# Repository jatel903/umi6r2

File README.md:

# UMI6R2
## Universal modbus inputs module
###### jatel.sk
**Specification:**  
Supply: 12 - 30V / 50mA  
Core: Arduino Nano  
Number of inputs: 6  
Input types: TTL / TTL with pull-up 2k2 / 0-10V / 1-10V / 0-20mA / 4-20mA  
Number of outputs: 2  
Output types: relay contact 10A/240VAC  
Communication: Modbus RTU 485  
Mounting: [DIN 4M](https://www.tme.eu/sk/en/details/4mh53_5/din-rail-mounting-enclosures/italtronic/)  

#### Description
Low cost universal modbus controll unit for low cost sensors and actuators from China:  
[NTC](https://www.aliexpress.com/item/1005001645557005.html?spm=a2g0o.productlist.0.0.187f54f5sMFDxZ&algo_pvid=9de88852-8f4a-408b-ad87-1dfdc50c90a6&algo_expid=9de88852-8f4a-408b-ad87-1dfdc50c90a6-12&btsid=2100bb5116140376819446860eae3f&ws_ab_test=searchweb0_0,searchweb201602_,searchweb201603_)  
 [Hall Flow Sensor](https://www.aliexpress.com/item/1005001652070023.html?spm=a2g0o.productlist.0.0.111d3f4bfW8KI7&algo_pvid=0e9d849e-a274-4857-9695-266535420252&algo_expid=0e9d849e-a274-4857-9695-266535420252-3&btsid=0b0a0ae216140368139255250ee091&ws_ab_test=searchweb0_0,searchweb201602_,searchweb201603_)  
[DHT22](https://www.aliexpress.com/item/32759901711.html?spm=a2g0o.productlist.0.0.7c9b27acyKxgzN&algo_pvid=cdfb1f8e-0449-4fde-b37e-72250bef6eec&algo_expid=cdfb1f8e-0449-4fde-b37e-72250bef6eec-1&btsid=2100bddf16140369182308517e6039&ws_ab_test=searchweb0_0,searchweb201602_,searchweb201603_)  
[DS18B20](https://www.aliexpress.com/item/4000895660165.html?spm=a2g0o.productlist.0.0.6e117a31a0Jav1&algo_pvid=1cb9bcee-23eb-4e23-812d-128fc839b4cb&algo_expid=1cb9bcee-23eb-4e23-812d-128fc839b4cb-4&btsid=2100bb5116140369607362637eb05f&ws_ab_test=searchweb0_0,searchweb201602_,searchweb201603_)  
[Pressure Sensor](https://www.aliexpress.com/item/1447040260.html?spm=a2g0o.productlist.0.0.542b418eIxJRxZ&algo_pvid=66da158e-1870-4b2f-a303-d273c240283c&algo_expid=66da158e-1870-4b2f-a303-d273c240283c-0&btsid=2100bdd516140372507935255e4c69&ws_ab_test=searchweb0_0,searchweb201602_,searchweb201603_)  
[Electric Valve](https://www.aliexpress.com/item/4000279793000.html?spm=a2g0o.productlist.0.0.721212089kHY2M&algo_pvid=9ae05a60-6b6b-4111-a46f-0fc823cf62b9&algo_expid=9ae05a60-6b6b-4111-a46f-0fc823cf62b9-30&btsid=0bb0624316140370036014582e4170&ws_ab_test=searchweb0_0,searchweb201602_,searchweb201603_)  
[Electric Solenoid Valve](https://www.aliexpress.com/item/4000067341651.html?spm=a2g0o.productlist.0.0.721212089kHY2M&algo_pvid=9ae05a60-6b6b-4111-a46f-0fc823cf62b9&algo_expid=9ae05a60-6b6b-4111-a46f-0fc823cf62b9-31&btsid=0bb0624316140370036014582e4170&ws_ab_test=searchweb0_0,searchweb201602_,searchweb201603_)  
etc...

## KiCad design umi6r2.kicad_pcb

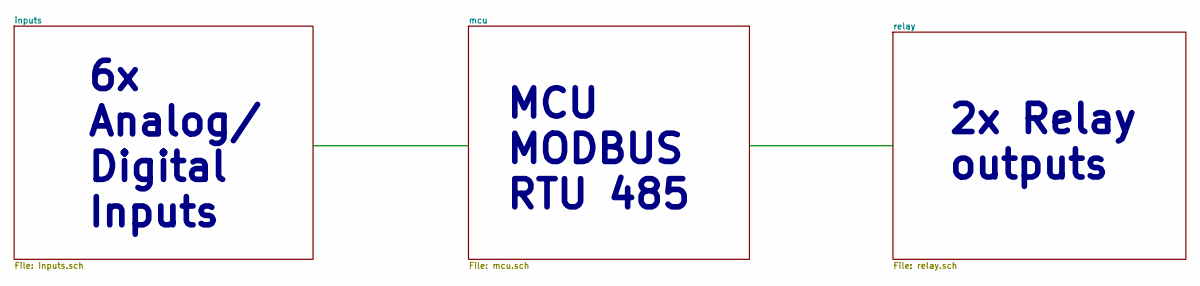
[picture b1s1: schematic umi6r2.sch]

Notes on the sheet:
MCU MODBUS RTU 485
2x Relay outputs
6x Analog/ Digital Inputs

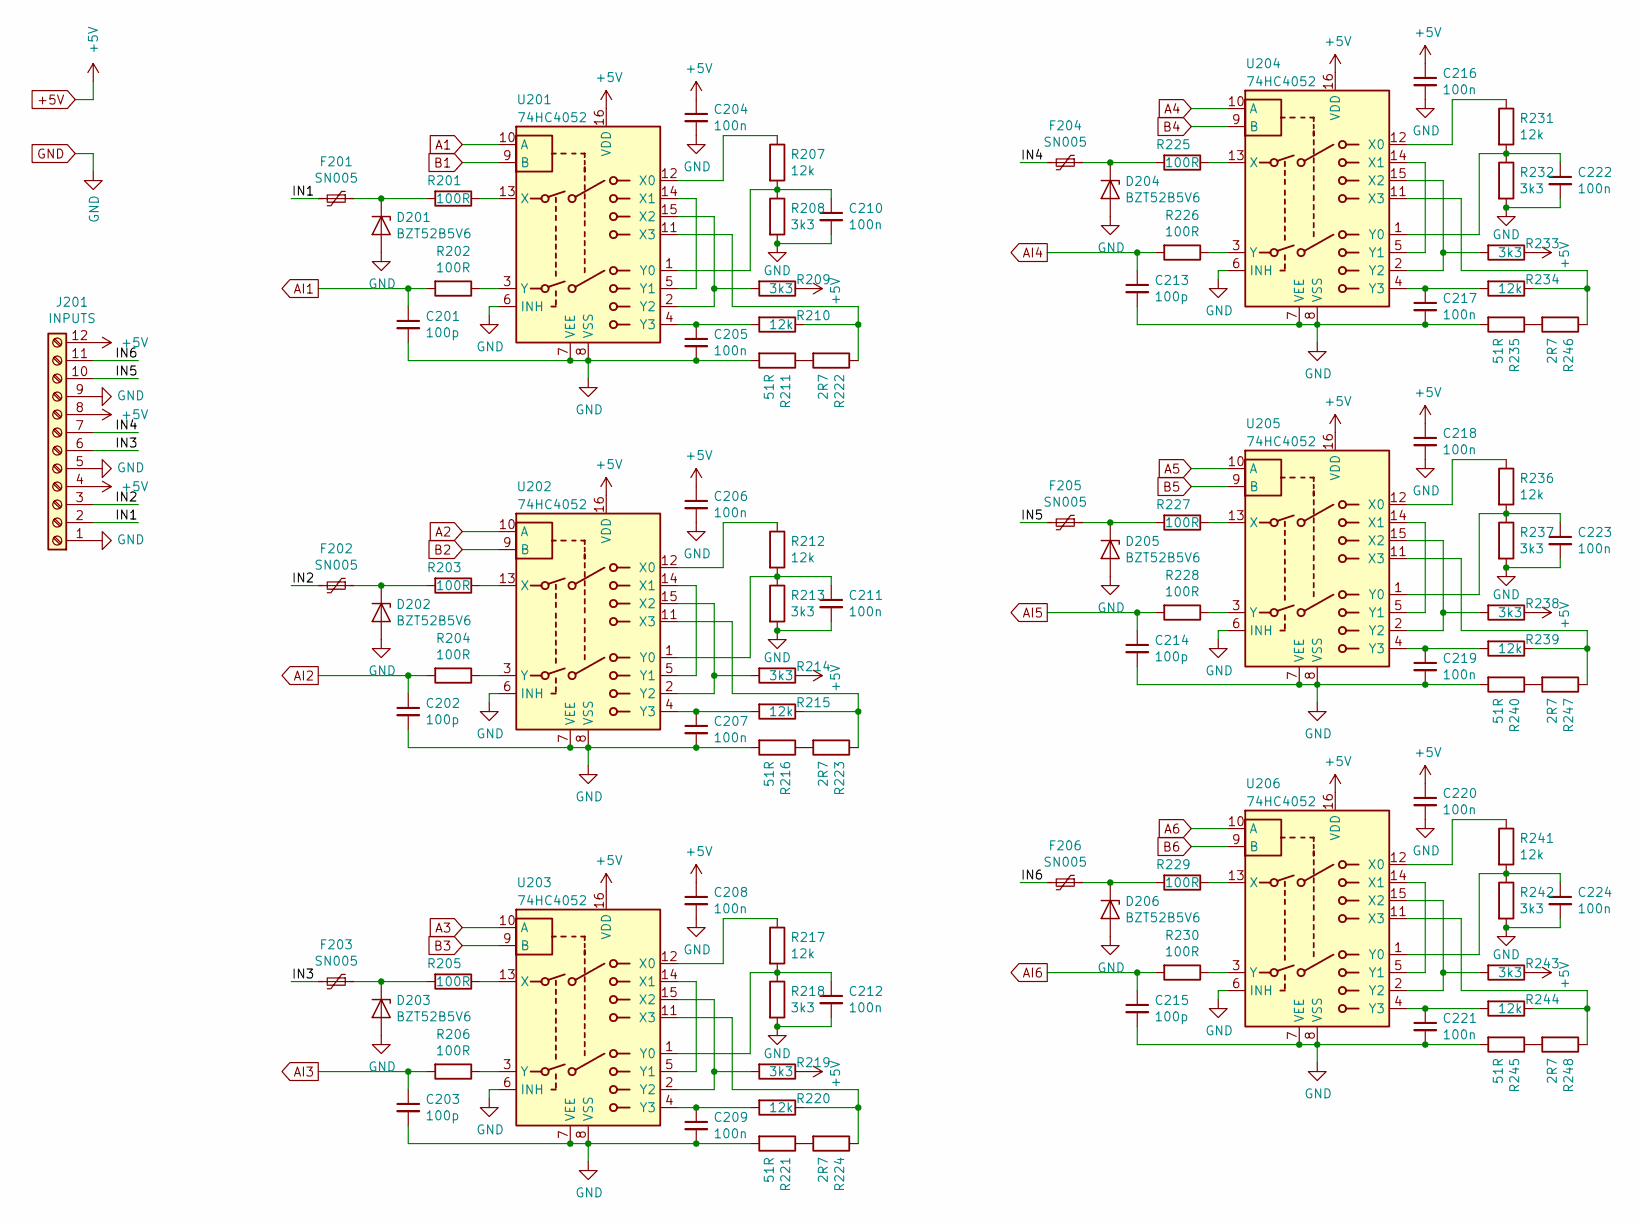
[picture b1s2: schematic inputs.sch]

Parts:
C201, C202, C203, C213, C214, C215: 100p; C_0805_2012Metric_Pad1.15x1.40mm_HandSolder
C204, C205, C206, C207, C208, C209, C210, C211, C212, C216, C217, C218, C219, C220, C221, C222, C223, C224: 100n; C_0805_2012Metric_Pad1.15x1.40mm_HandSolder
D201, D202, D203, D204, D205, D206: BZT52B5V6; D_SOD-123
F201, F202, F203, F204, F205, F206: SN005; R_1206_3216Metric_Pad1.42x1.75mm_HandSolder
J201: INPUTS; TerminalBlock_Phoenix_MKDS-1,5-12-5.08_1x12_P5.08mm_Horizon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
R201, R202, R203, R204, R205, R206, R225, R226, R227, R228, R229, R230: 100R; R_0805_2012Metric_Pad1.15x1.40mm_HandSolder
R207, R210, R212, R215, R217, R220, R231, R234, R236, R239, R241, R244: 12k; R_0805_2012Metric_Pad1.15x1.40mm_HandSolder
R208, R209, R213, R214, R218, R219, R232, R233, R237, R238, R242, R243: 3k3; R_0805_2012Metric_Pad1.15x1.40mm_HandSolder
R211, R216, R221, R235, R240, R245: 51R; R_0805_2012Metric_Pad1.15x1.40mm_HandSolder
R222, R223, R224, R246, R247, R248: 2R7; R_0805_2012Metric_Pad1.15x1.40mm_HandSolder
U201, U202, U203, U204, U205, U206: 74HC4052; SOIC-16_3.9x9.9mm_P1.27mm

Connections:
+5V: C204.1, C206.1, C208.1, C216.1, C218.1, C220.1, J201.4, J201.8, J201.12, R209.1, R214.1, R219.1, R233.1, R238.1, R243.1, U201.16 (VDD), U202.16 (VDD), U203.16 (VDD), U204.16 (VDD), U205.16 (VDD), U206.16 (VDD); also elsewhere on the board
/inputs/IN1: F201.2, J201.2
/inputs/IN2: F202.2, J201.3
/inputs/IN3: F203.2, J201.6
/inputs/IN4: F204.2, J201.7
/inputs/IN5: F205.2, J201.10
/inputs/IN6: F206.2, J201.11
A1: U201.10 (A); also elsewhere on the board
A2: U202.10 (A); also elsewhere on the board
A3: U203.10 (A); also elsewhere on the board
A4: U204.10 (A); also elsewhere on the board
A5: U205.10 (A); also elsewhere on the board
A6: U206.10 (A); also elsewhere on the board
AI1: C201.1, R202.2; also elsewhere on the board
AI2: C202.1, R204.2; also elsewhere on the board
AI3: C203.1, R206.2; also elsewhere on the board
AI4: C213.1, R226.2; also elsewhere on the board
AI5: C214.1, R228.2; also elsewhere on the board
AI6: C215.1, R230.2; also elsewhere on the board
B1: U201.9 (B); also elsewhere on the board
B2: U202.9 (B); also elsewhere on the board
B3: U203.9 (B); also elsewhere on the board
B4: U204.9 (B); also elsewhere on the board
B5: U205.9 (B); also elsewhere on the board
B6: U206.9 (B); also elsewhere on the board
GND: C201.2, C202.2, C203.2, C204.2, C205.2, C206.2, C207.2, C208.2, C209.2, C210.2, C211.2, C212.2, C213.2, C214.2, C215.2, C216.2, C217.2, C218.2, C219.2, C220.2, C221.2, C222.2, C223.2, C224.2, D201.2 (A), D202.2 (A), D203.2 (A), D204.2 (A), D205.2 (A), D206.2 (A), J201.1, J201.5, J201.9, R208.2, R211.2, R213.2, R216.2, R218.2, R221.2, R232.2, R235.2, R237.2, R240.2, R242.2, R245.2, U201.6 (INH), U201.7 (VEE), U201.8 (VSS), U202.6 (INH), U202.7 (VEE), U202.8 (VSS), U203.6 (INH), U203.7 (VEE), U203.8 (VSS), U204.6 (INH), U204.7 (VEE), U204.8 (VSS), U205.6 (INH), U205.7 (VEE), U205.8 (VSS), U206.6 (INH), U206.7 (VEE), U206.8 (VSS); also elsewhere on the board
unnamed: C205.1, R210.2, U201.4 (Y3)
unnamed: C207.1, R215.2, U202.4 (Y3)
unnamed: C209.1, R220.2, U203.4 (Y3)
unnamed: C210.1, R207.2, R208.1, U201.1 (Y0)
unnamed: C211.1, R212.2, R213.1, U202.1 (Y0)
unnamed: C212.1, R217.2, R218.1, U203.1 (Y0)
unnamed: C217.1, R234.2, U204.4 (Y3)
unnamed: C219.1, R239.2, U205.4 (Y3)
unnamed: C221.1, R244.2, U206.4 (Y3)
unnamed: C222.1, R231.2, R232.1, U204.1 (Y0)
unnamed: C223.1, R236.2, R237.1, U205.1 (Y0)
unnamed: C224.1, R241.2, R242.1, U206.1 (Y0)
unnamed: D201.1 (K), F201.1, R201.2
unnamed: D202.1 (K), F202.1, R203.2
unnamed: D203.1 (K), F203.1, R205.2
unnamed: D204.1 (K), F204.1, R225.2
unnamed: D205.1 (K), F205.1, R227.2
unnamed: D206.1 (K), F206.1, R229.2
unnamed: R201.1, U201.13 (X)
unnamed: R202.1, U201.3 (Y)
unnamed: R203.1, U202.13 (X)
unnamed: R204.1, U202.3 (Y)
unnamed: R205.1, U203.13 (X)
unnamed: R206.1, U203.3 (Y)
unnamed: R207.1, U201.12 (X0)
unnamed: R209.2, U201.2 (Y2), U201.15 (X2)
unnamed: R210.1, R222.1, U201.11 (X3)
unnamed: R211.1, R222.2
unnamed: R212.1, U202.12 (X0)
unnamed: R214.2, U202.2 (Y2), U202.15 (X2)
unnamed: R215.1, R223.1, U202.11 (X3)
unnamed: R216.1, R223.2
unnamed: R217.1, U203.12 (X0)
unnamed: R219.2, U203.2 (Y2), U203.15 (X2)
unnamed: R220.1, R224.1, U203.11 (X3)
unnamed: R221.1, R224.2
unnamed: R225.1, U204.13 (X)
unnamed: R226.1, U204.3 (Y)
unnamed: R227.1, U205.13 (X)
unnamed: R228.1, U205.3 (Y)
unnamed: R229.1, U206.13 (X)
unnamed: R230.1, U206.3 (Y)
unnamed: R231.1, U204.12 (X0)
unnamed: R233.2, U204.2 (Y2), U204.15 (X2)
unnamed: R234.1, R246.1, U204.11 (X3)
unnamed: R235.1, R246.2
unnamed: R236.1, U205.12 (X0)
unnamed: R238.2, U205.2 (Y2), U205.15 (X2)
unnamed: R239.1, R247.1, U205.11 (X3)
unnamed: R240.1, R247.2
unnamed: R241.1, U206.12 (X0)
unnamed: R243.2, U206.2 (Y2), U206.15 (X2)
unnamed: R244.1, R248.1, U206.11 (X3)
unnamed: R245.1, R248.2
unnamed: U201.5 (Y1), U201.14 (X1)
unnamed: U202.5 (Y1), U202.14 (X1)
unnamed: U203.5 (Y1), U203.14 (X1)
unnamed: U204.5 (Y1), U204.14 (X1)
unnamed: U205.5 (Y1), U205.14 (X1)
unnamed: U206.5 (Y1), U206.14 (X1)

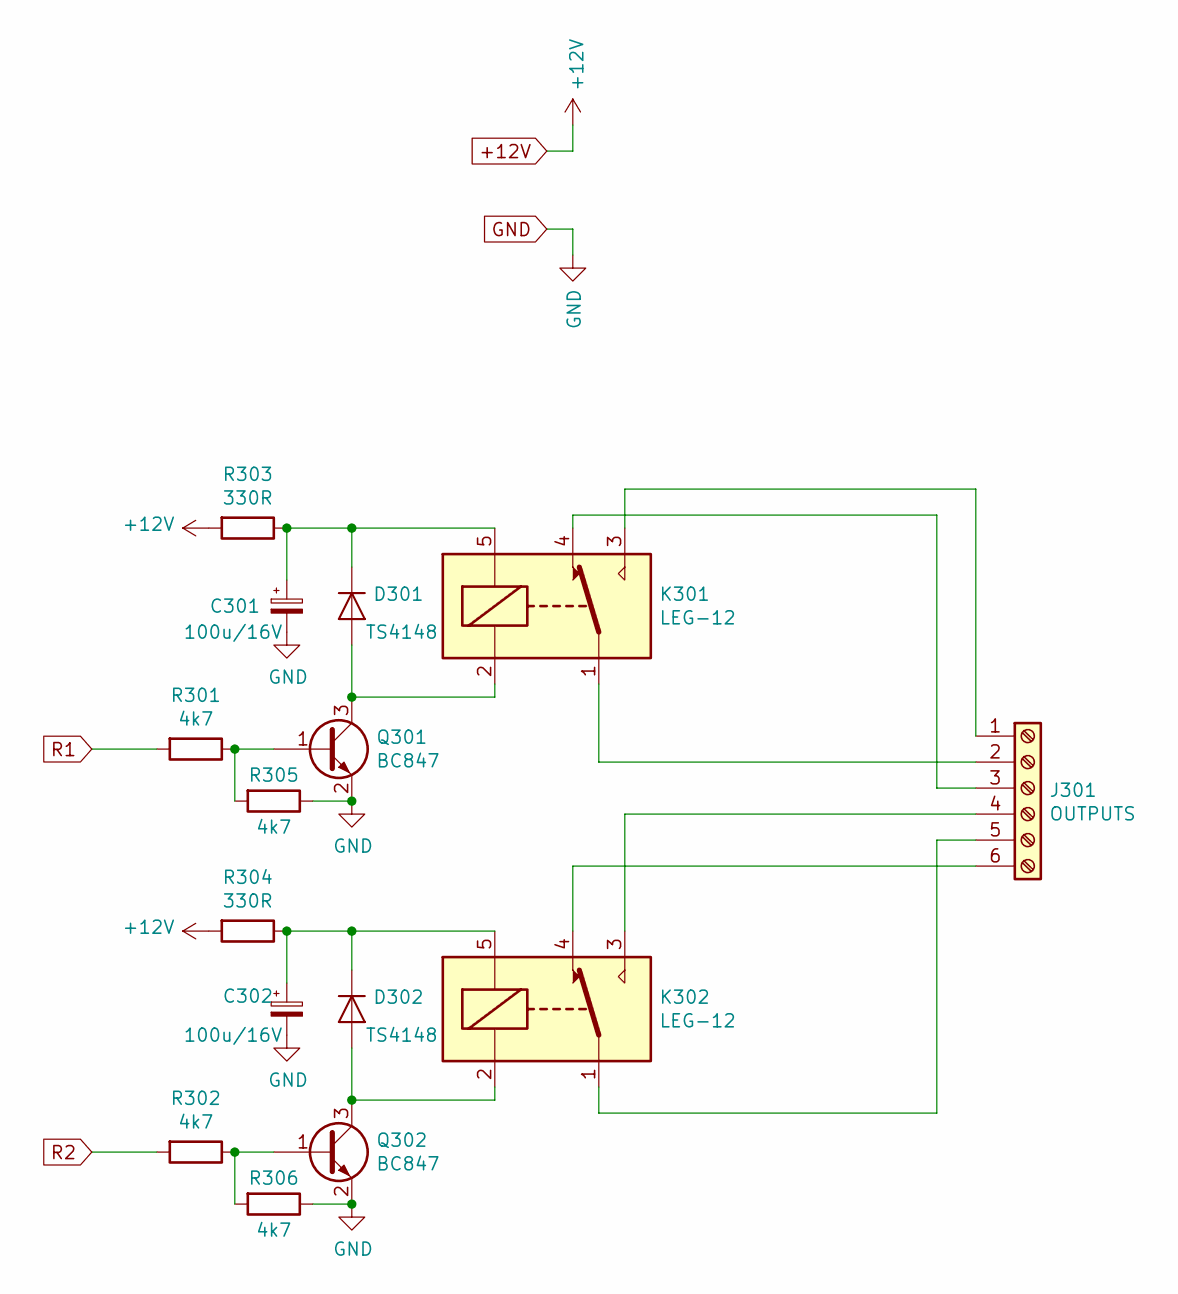
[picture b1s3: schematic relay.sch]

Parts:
C301, C302: 100u/16V; CP_Radial_D5.0mm_P2.50mm
D301, D302: TS4148; D_0805_2012Metric
J301: OUTPUTS; TerminalBlock_Phoenix_MKDS-1,5-6-5.08_1x06_P5.08mm_Horizont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
K301, K302: LEG-12; Relay_SPDT_RAYEX ELEC_LEG_Series_Form_1C
Q301, Q302: BC847; SOT-23
R301, R302, R305, R306: 4k7; R_0805_2012Metric_Pad1.15x1.40mm_HandSolder
R303, R304: 330R; R_0805_2012Metric_Pad1.15x1.40mm_HandSolder

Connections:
+12V: R303.2, R304.2; also elsewhere on the board
GND: C301.2, C302.2, Q301.2 (E), Q302.2 (E), R305.1, R306.1; also elsewhere on the board
unnamed: C301.1, D301.1 (K), K301.5 (coil), R303.1
unnamed: C302.1, D302.1 (K), K302.5 (coil), R304.1
unnamed: D301.2 (A), K301.2 (coil), Q301.3 (C)
unnamed: D302.2 (A), K302.2 (coil), Q302.3 (C)
unnamed: J301.1, K301.3 (NO)
unnamed: J301.2, K301.1 (com)
unnamed: J301.3, K301.4 (NC)
unnamed: J301.4, K302.3 (NO)
unnamed: J301.5, K302.1 (com)
unnamed: J301.6, K302.4 (NC)
unnamed: Q301.1 (B), R301.1, R305.2
unnamed: Q302.1 (B), R302.1, R306.2
R1: R301.2; also elsewhere on the board
R2: R302.2; also elsewhere on the board

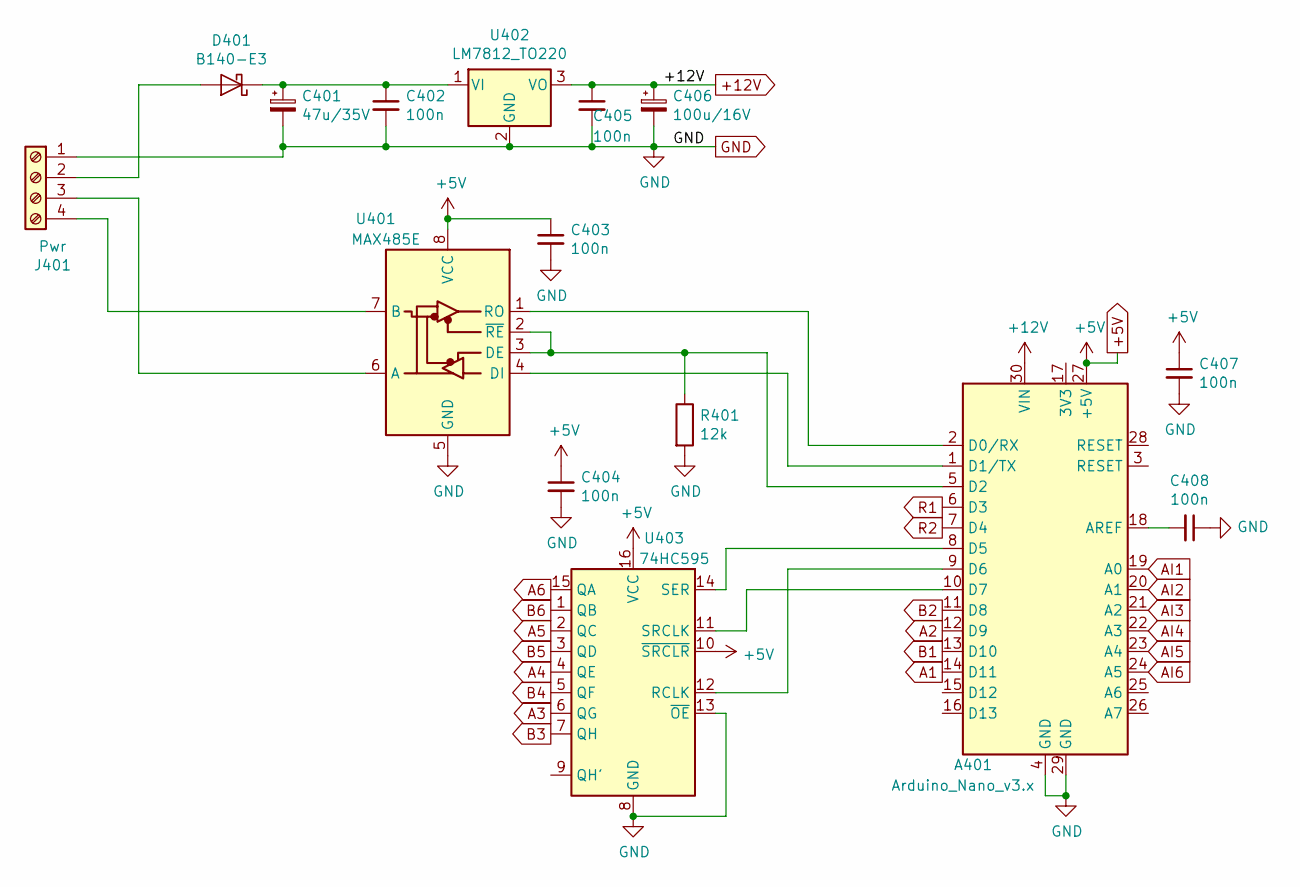
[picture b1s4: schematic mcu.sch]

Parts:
A401: Arduino_Nano_v3.x; Arduino_Nano
C401: 47u/35V; CP_Radial_D5.0mm_P2.50mm
C402, C403, C404, C405, C407, C408: 100n; C_0805_2012Metric_Pad1.15x1.40mm_HandSolder
C406: 100u/16V; CP_Radial_D5.0mm_P2.50mm
D401: B140-E3; D_SMA
J401: Pwr; TerminalBlock_Phoenix_MKDS-1,5-4-5.08_1x04_P5.08mm_Horizont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
R401: 12k; R_0805_2012Metric_Pad1.15x1.40mm_HandSolder
U401: MAX485E; SOIC-8_3.9x4.9mm_P1.27mm
U402: LM7812_TO220; TO-220-3_Vertical
U403: 74HC595; SOIC-16_3.9x9.9mm_P1.27mm

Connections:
+5V: A401.27 (+5V), C403.1, C404.1, C407.1, U401.8 (VCC), U403.10 (~SRCLR), U403.16 (VCC); also elsewhere on the board
+12V: A401.30 (VIN), C405.1, C406.1, U402.3 (VO); also elsewhere on the board
A1: A401.14 (D11); also elsewhere on the board
A2: A401.12 (D9); also elsewhere on the board
A3: U403.6 (QG); also elsewhere on the board
A4: U403.4 (QE); also elsewhere on the board
A5: U403.2 (QC); also elsewhere on the board
A6: U403.15 (QA); also elsewhere on the board
AI1: A401.19 (A0); also elsewhere on the board
AI2: A401.20 (A1); also elsewhere on the board
AI3: A401.21 (A2); also elsewhere on the board
AI4: A401.22 (A3); also elsewhere on the board
AI5: A401.23 (A4); also elsewhere on the board
AI6: A401.24 (A5); also elsewhere on the board
B1: A401.13 (D10); also elsewhere on the board
B2: A401.11 (D8); also elsewhere on the board
B3: U403.7 (QH); also elsewhere on the board
B4: U403.5 (QF); also elsewhere on the board
B5: U403.3 (QD); also elsewhere on the board
B6: U403.1 (QB); also elsewhere on the board
GND: A401.4 (GND), A401.29 (GND), C401.2, C402.2, C403.2, C404.2, C405.2, C406.2, C407.2, C408.1, J401.1, R401.2, U401.5 (GND), U402.2 (GND), U403.8 (GND), U403.13 (~OE); also elsewhere on the board
unnamed: A401.1 (D1/TX), U401.4 (DI)
unnamed: A401.2 (D0/RX), U401.1 (RO)
unnamed: A401.5 (D2), R401.1, U401.2 (~RE), U401.3 (DE)
unnamed: A401.8 (D5), U403.14 (SER)
unnamed: A401.9 (D6), U403.12 (RCLK)
unnamed: A401.10 (D7), U403.11 (SRCLK)
unnamed: A401.18 (AREF), C408.2
unnamed: C401.1, C402.1, D401.1 (K), U402.1 (VI)
unnamed: D401.2 (A), J401.2
unnamed: J401.3, U401.6 (A)
unnamed: J401.4, U401.7 (B)
R1: A401.6 (D3); also elsewhere on the board
R2: A401.7 (D4); also elsewhere on the board

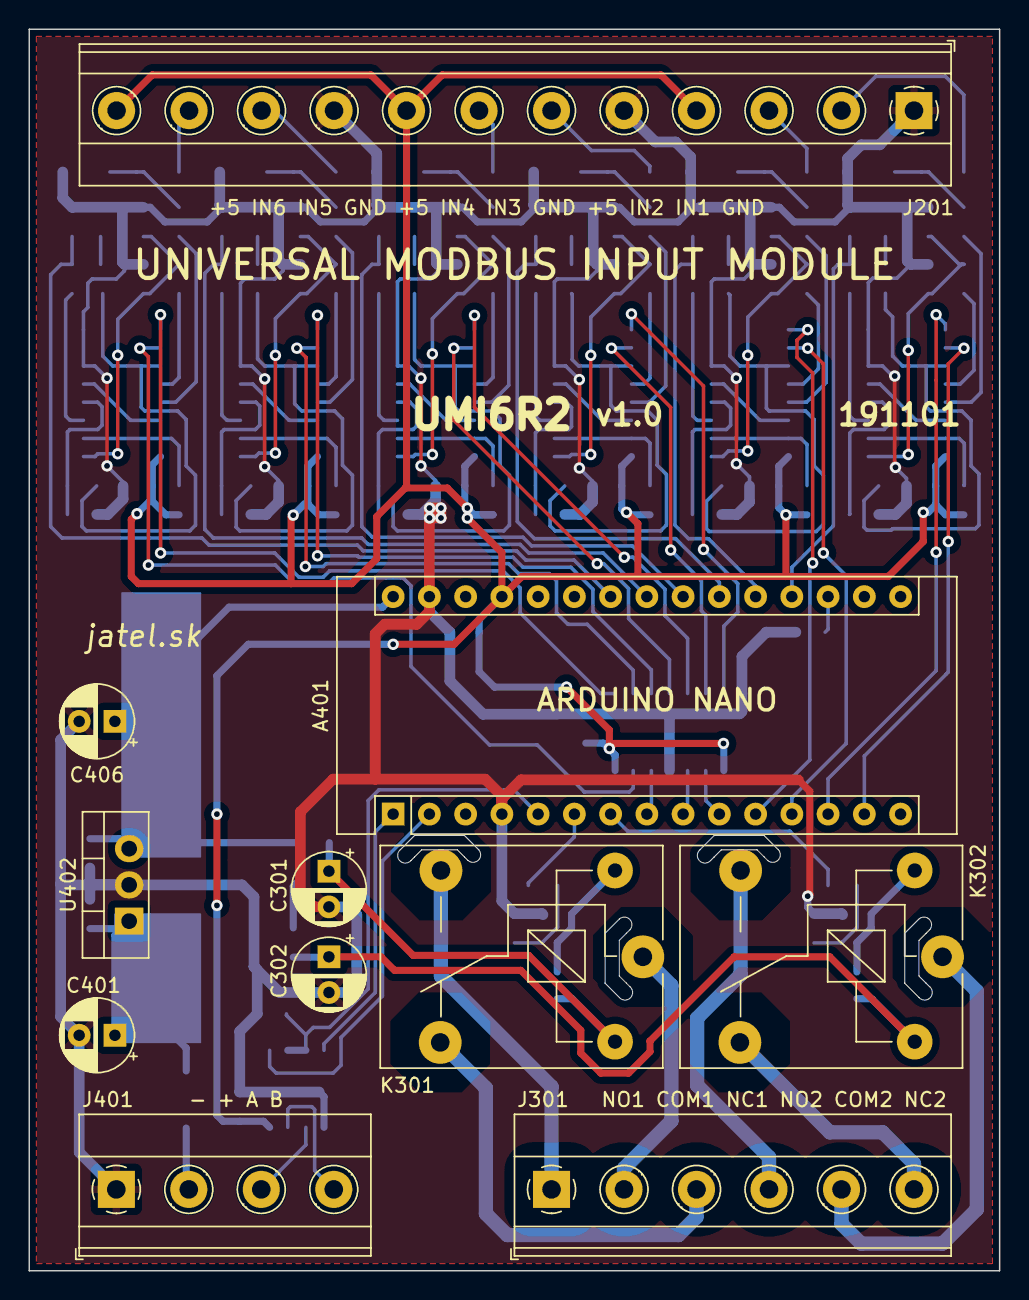
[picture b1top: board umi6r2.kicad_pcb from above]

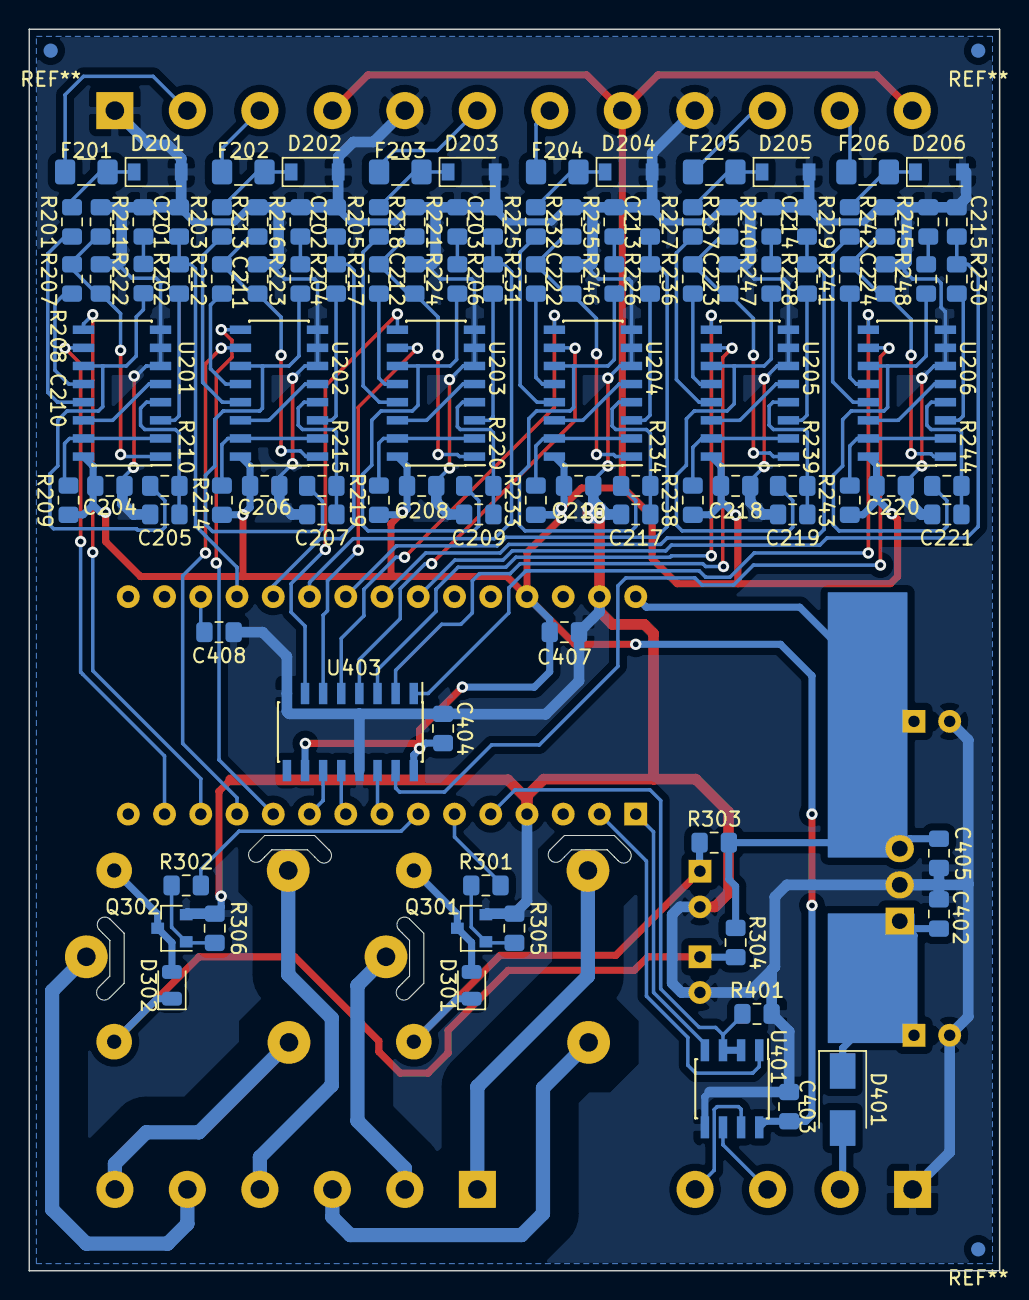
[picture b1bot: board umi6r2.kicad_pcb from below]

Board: 2 copper layers, 68.0 x 87.0 mm, 121 parts (110 on the bottom side), 112 nets.

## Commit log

2021-02-22 init
